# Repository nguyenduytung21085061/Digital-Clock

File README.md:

# 🕒 Digital Clock với ATtiny2313

## 📌 Giới thiệu

Dự án này là một **đồng hồ số (Digital Clock)** sử dụng vi điều khiển **ATtiny2313**, có khả năng:

* Hiển thị thời gian thực (RTC)
* Đo nhiệt độ/độ ẩm
* Cài đặt giờ báo thức
* Phát còi buzzer khi đến giờ

Hiển thị được thực hiện thông qua LED 7 đoạn **TM1637**, và người dùng tương tác bằng **4 nút nhấn (button)**.

---

## ⚙️ Phần cứng sử dụng

| Thành phần | Mô tả                                   |
| ---------- | --------------------------------------- |
| ATtiny2313 | Vi điều khiển chính                     |
| DS1302     | Module RTC (Real-Time Clock)            |
| DHT11      | Cảm biến nhiệt độ và độ ẩm              |
| TM1637     | LED 7 đoạn 4 digit                      |
| Button x4  | Điều khiển (mode, tăng, giảm, xác nhận) |
| Buzzer     | Còi báo thức                            |

---

## 🔌 Kết nối phần cứng

### 1. Vi điều khiển ATtiny2313

ATtiny2313 là bộ điều khiển trung tâm, chịu trách nhiệm:

* Giao tiếp với các module ngoại vi
* Xử lý dữ liệu thời gian và cảm biến
* Điều khiển hiển thị và buzzer
* Nhận input từ các nút nhấn

---

### 2. Module RTC DS1302

Giao tiếp sử dụng chuẩn **3-wire (bit-banging)**:

| Tín hiệu | Chân MCU |
| -------- | -------- |
| CE       | PD3      |
| SCLK     | PD1      |
| IO       | PD2      |

👉 Chức năng:

* Lưu và cung cấp thời gian thực (giờ, phút, giây)

---

### 3. Cảm biến DHT11

Giao tiếp theo chuẩn **1-wire custom protocol**:

| Tín hiệu | Chân MCU |
| -------- | -------- |
| DATA     | PD4      |

👉 Chức năng:

* Đo nhiệt độ môi trường
* Đo độ ẩm không khí

---

### 4. LED 7 đoạn TM1637

Giao tiếp **2-wire (CLK + DIO)**:

| Tín hiệu | Chân MCU |
| -------- | -------- |
| DIO      | PB0      |
| CLK      | PD6      |

👉 Chức năng:

* Hiển thị thời gian (HH:MM)
* Hiển thị nhiệt độ

---

### 5. Hệ thống nút nhấn

Sử dụng 4 nút để điều khiển hệ thống:

| Nút      | Chân MCU | Chức năng     |
| -------- | -------- | ------------- |
| Button 1 | PB1      | Chuyển chế độ |
| Button 2 | PB2      | Tăng giá trị  |
| Button 3 | PB3      | Giảm giá trị  |
| Button 4 | PB4      | Xác nhận / OK |

---

### 6. Buzzer

| Thiết bị | Chân MCU |
| -------- | -------- |
| Buzzer   | PD0      |

👉 Chức năng:

* Phát âm thanh khi đến giờ báo thức

---

## 📌 Ghi chú

* Toàn bộ chân được định nghĩa trong file `macro.h`
* Hệ thống sử dụng **GPIO trực tiếp**, không dùng peripheral chuyên dụng
* Các giao thức:

  * DS1302
  * DHT11
  * TM1637
    đều được triển khai bằng phương pháp **bit-banging**

---

## 🔄 Chế độ hoạt động

Hệ thống có các mode chính:

### 🟢 Mode 1: Hiển thị thời gian (RTC)

* Đọc dữ liệu từ DS1302
* Hiển thị lên TM1637 theo dạng:

  ```
  HH:MM
  ```

---

### 🟡 Mode 2: Hiển thị nhiệt độ (DHT11)

* Đọc dữ liệu từ DHT11
* Hiển thị:

  ```
  t°C:h% 
  ```

---

### 🔵 Mode 3: Cài đặt giờ

* Dùng button để:

  * Tăng/giảm giờ
  * Xác nhận

---

### 🟣 Mode 4: Cài đặt phút

* Tương tự set giờ
* Sau khi xác nhận → lưu vào biến alarm

---

## ⏰ Báo thức (Alarm)

* Người dùng cài:

  * Giờ
  * Phút
* Khi thời gian thực (DS1302) == thời gian cài:

  * Buzzer sẽ kêu

👉 Có thể:

* Tắt bằng nút nhấn
* Hoặc tự tắt sau thời gian

---

## 📡 Giao tiếp dữ liệu

### DS1302

* Gửi command → đọc/ghi thanh ghi
* Khung truyền khi gửi lệnh ghi vào giờ:

---

### DHT11

* MCU gửi start signal
* DHT11 phản hồi
* Trả về 40 bit:

  ```
  Humidity + Temp + Checksum
  ```

---

### TM1637

* Gửi từng byte để hiển thị LED
* Điều khiển:

  * Segment
  * Brightness

---

## 🚀 Tính năng nổi bật

* Hiển thị thời gian thực
* Đo nhiệt độ môi trường
* Có báo thức
* Giao diện đơn giản bằng nút nhấn
* Chạy trên MCU nhỏ (ATtiny2313)

---

## 📷 Demo (nếu có)

> Thêm hình hoặc video tại đây

---

## 🛠️ Hướng phát triển

* Thêm hiển thị độ ẩm
* Thêm nhiều alarm
* Thêm lưu EEPROM
* Nâng cấp sang MCU mạnh hơn (ESP32 😎)

---

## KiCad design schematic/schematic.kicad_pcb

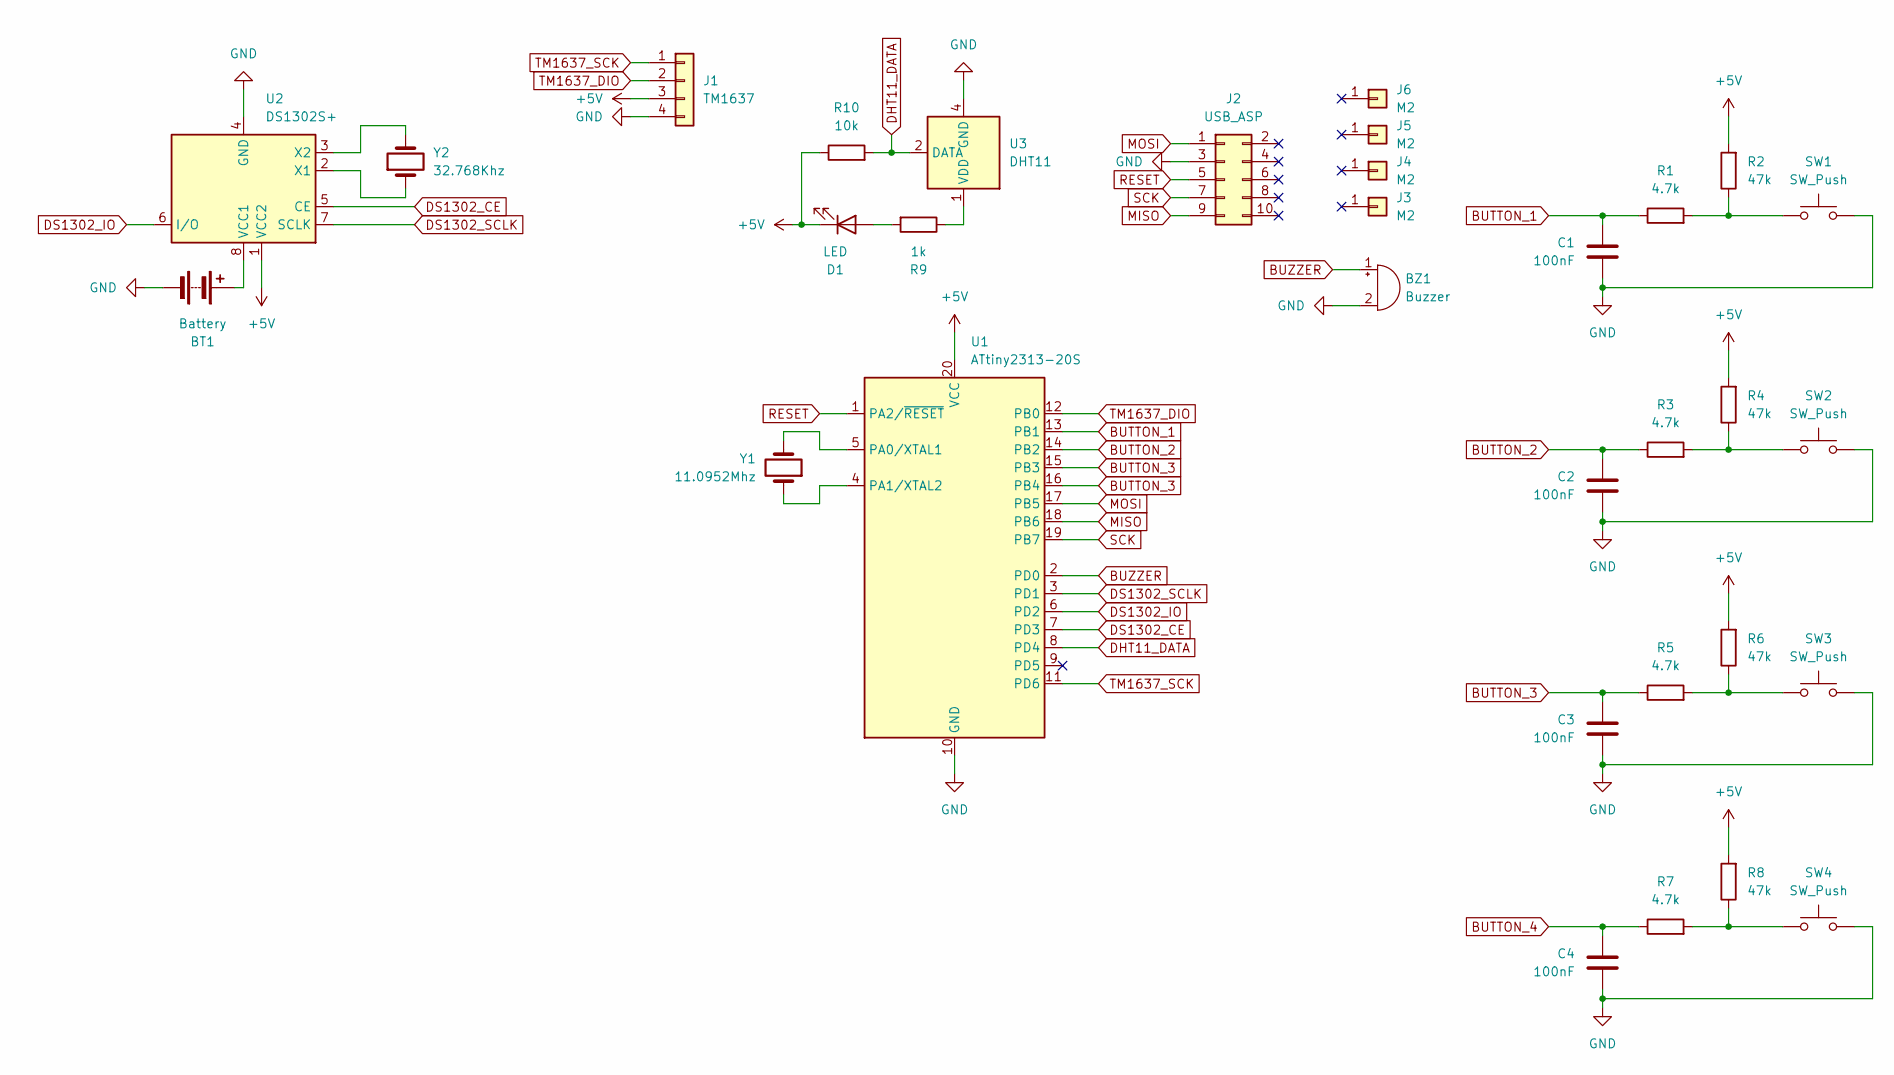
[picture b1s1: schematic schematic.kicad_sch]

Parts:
BT1: Battery; Battery_Panasonic_CR2032-HFN_Horizontal_CircularHoles
BZ1: Buzzer; Buzzer_12x9.5RM7.6
C1, C2, C3, C4: 100nF; C_Disc_D3.4mm_W2.1mm_P2.50mm
D1: LED; LED_D3.0mm
J1: TM1637; PinHeader_1x04_P2.54mm_Vertical
J2: USB_ASP; IDC-Header_2x05_P2.54mm_Vertical
J3, J4, J5, J6: M2; MountingHole_2.2mm_M2_Pad_Via
R1, R3, R5, R7: 4.7k; R_Axial_DIN0207_L6.3mm_D2.5mm_P7.62mm_Horizontal
R2, R4, R6, R8: 47k; R_Axial_DIN0207_L6.3mm_D2.5mm_P7.62mm_Horizontal
R9: 1k; R_Axial_DIN0207_L6.3mm_D2.5mm_P7.62mm_Horizontal
R10: 10k; R_Axial_DIN0207_L6.3mm_D2.5mm_P7.62mm_Horizontal
SW1, SW2, SW3, SW4: SW_Push; SW_PUSH_1P1T_6x3.5mm_H5.0_APEM_MJTP1250
U1: ATtiny2313-20S; SOIC-20W_7.5x12.8mm_P1.27mm
U2: DS1302S+; SO-8_5.3x6.2mm_P1.27mm
U3: DHT11; Aosong_DHT11_5.5x12.0_P2.54mm
Y1: 11.0952Mhz; Crystal_HC49-U_Vertical
Y2: 32.768Khz; Crystal_DS26_D2.0mm_L6.0mm_Vertical

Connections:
+5V: D1.1 (K), J1.3, R2.2, R4.2, R6.2, R8.2, R10.1, U1.20 (VCC), U2.1 (VCC2)
BUTTON_1: C1.1, R1.1, U1.13 (PB1)
BUTTON_2: C2.1, R3.1, U1.14 (PB2)
BUTTON_3: C3.1, R5.1, U1.15 (PB3), U1.16 (PB4)
BUTTON_4: C4.1, R7.1
BUZZER: BZ1.1 (+), U1.2 (PD0)
DHT11_DATA: R10.2, U1.8 (PD4), U3.2 (DATA)
DS1302_CE: U1.7 (PD3), U2.5 (CE)
DS1302_IO: U1.6 (PD2), U2.6 (I/O)
DS1302_SCLK: U1.3 (PD1), U2.7 (SCLK)
GND: BT1.2 (-), BZ1.2 (-), C1.2, C2.2, C3.2, C4.2, J1.4, J2.3, SW1.2, SW2.2, SW3.2, SW4.2, U1.10 (GND), U2.4 (GND), U3.4 (GND)
MISO: J2.9, U1.18 (PB6)
MOSI: J2.1, U1.17 (PB5)
unnamed: BT1.1 (+), U2.8 (VCC1)
unnamed: D1.2 (A), R9.2
unnamed: R1.2, R2.1, SW1.1
unnamed: R3.2, R4.1, SW2.1
unnamed: R5.2, R6.1, SW3.1
unnamed: R7.2, R8.1, SW4.1
unnamed: U1.5 (PA0/XTAL1), Y1.2
unnamed: U1.4 (PA1/XTAL2), Y1.1
unnamed: U2.2 (X1), Y2.1
unnamed: U2.3 (X2), Y2.2
unnamed: R9.1, U3.1 (VDD)
RESET: J2.5, U1.1 (PA2/~RESET)
SCK: J2.7, U1.19 (PB7)
TM1637_DIO: J1.2, U1.12 (PB0)
TM1637_SCK: J1.1, U1.11 (PD6)

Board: 2 copper layers, 32 parts (0 on the bottom side), 28 nets, no tracks yet.

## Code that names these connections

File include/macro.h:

#ifndef __MACRO_H__
#define __MACRO_H__

#include <avr/io.h>

#define BUTTON_1        PB1 
#define BUTTON_2        PB2 
#define BUTTON_3        PB3 
#define BUTTON_4        PB4 
#define DIO_TM1637      PB0 
#define CLK_TM1637      PD6 
#define P_DHT11         PD4 
#define LOG             PD4 
#define RESET_DS1302    PD3 
#define IO_DS1302       PD2 
#define SCLK_DS1302     PD1 
#define P_BUZZER        PD0

#endif // __MACRO_H__

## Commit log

2026-05-04 complete sensors and actuators project
2026-05-04 documents use project
2026-05-05 backup data
2026-05-05 REAME.md
2026-05-08 Upload schematics boards
2026-05-09 Add spec.md
2026-05-30 add view and video product
